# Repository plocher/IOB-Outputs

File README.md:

# IOB-Outputs
## License: CERN Open Hardware Licence v1.2

Output only - non-inverting Open Drain current sink
New IOB design

PNP Ready: Panelized IOB quad "output board", used for driving LEDS and other devices from the [I2C-7311](/pages/I2C-7311) IO expansion board

Features:

* 5v or 9-12v supply,
* Open Drain outputs
* pins are active low

IO4:

* pin 1: 5vDC
* pin 2: !OUT1
* pin 3: !OUT2
* pin 4: !OUT3
* pin 5: !OUT4
* pin 6: GND

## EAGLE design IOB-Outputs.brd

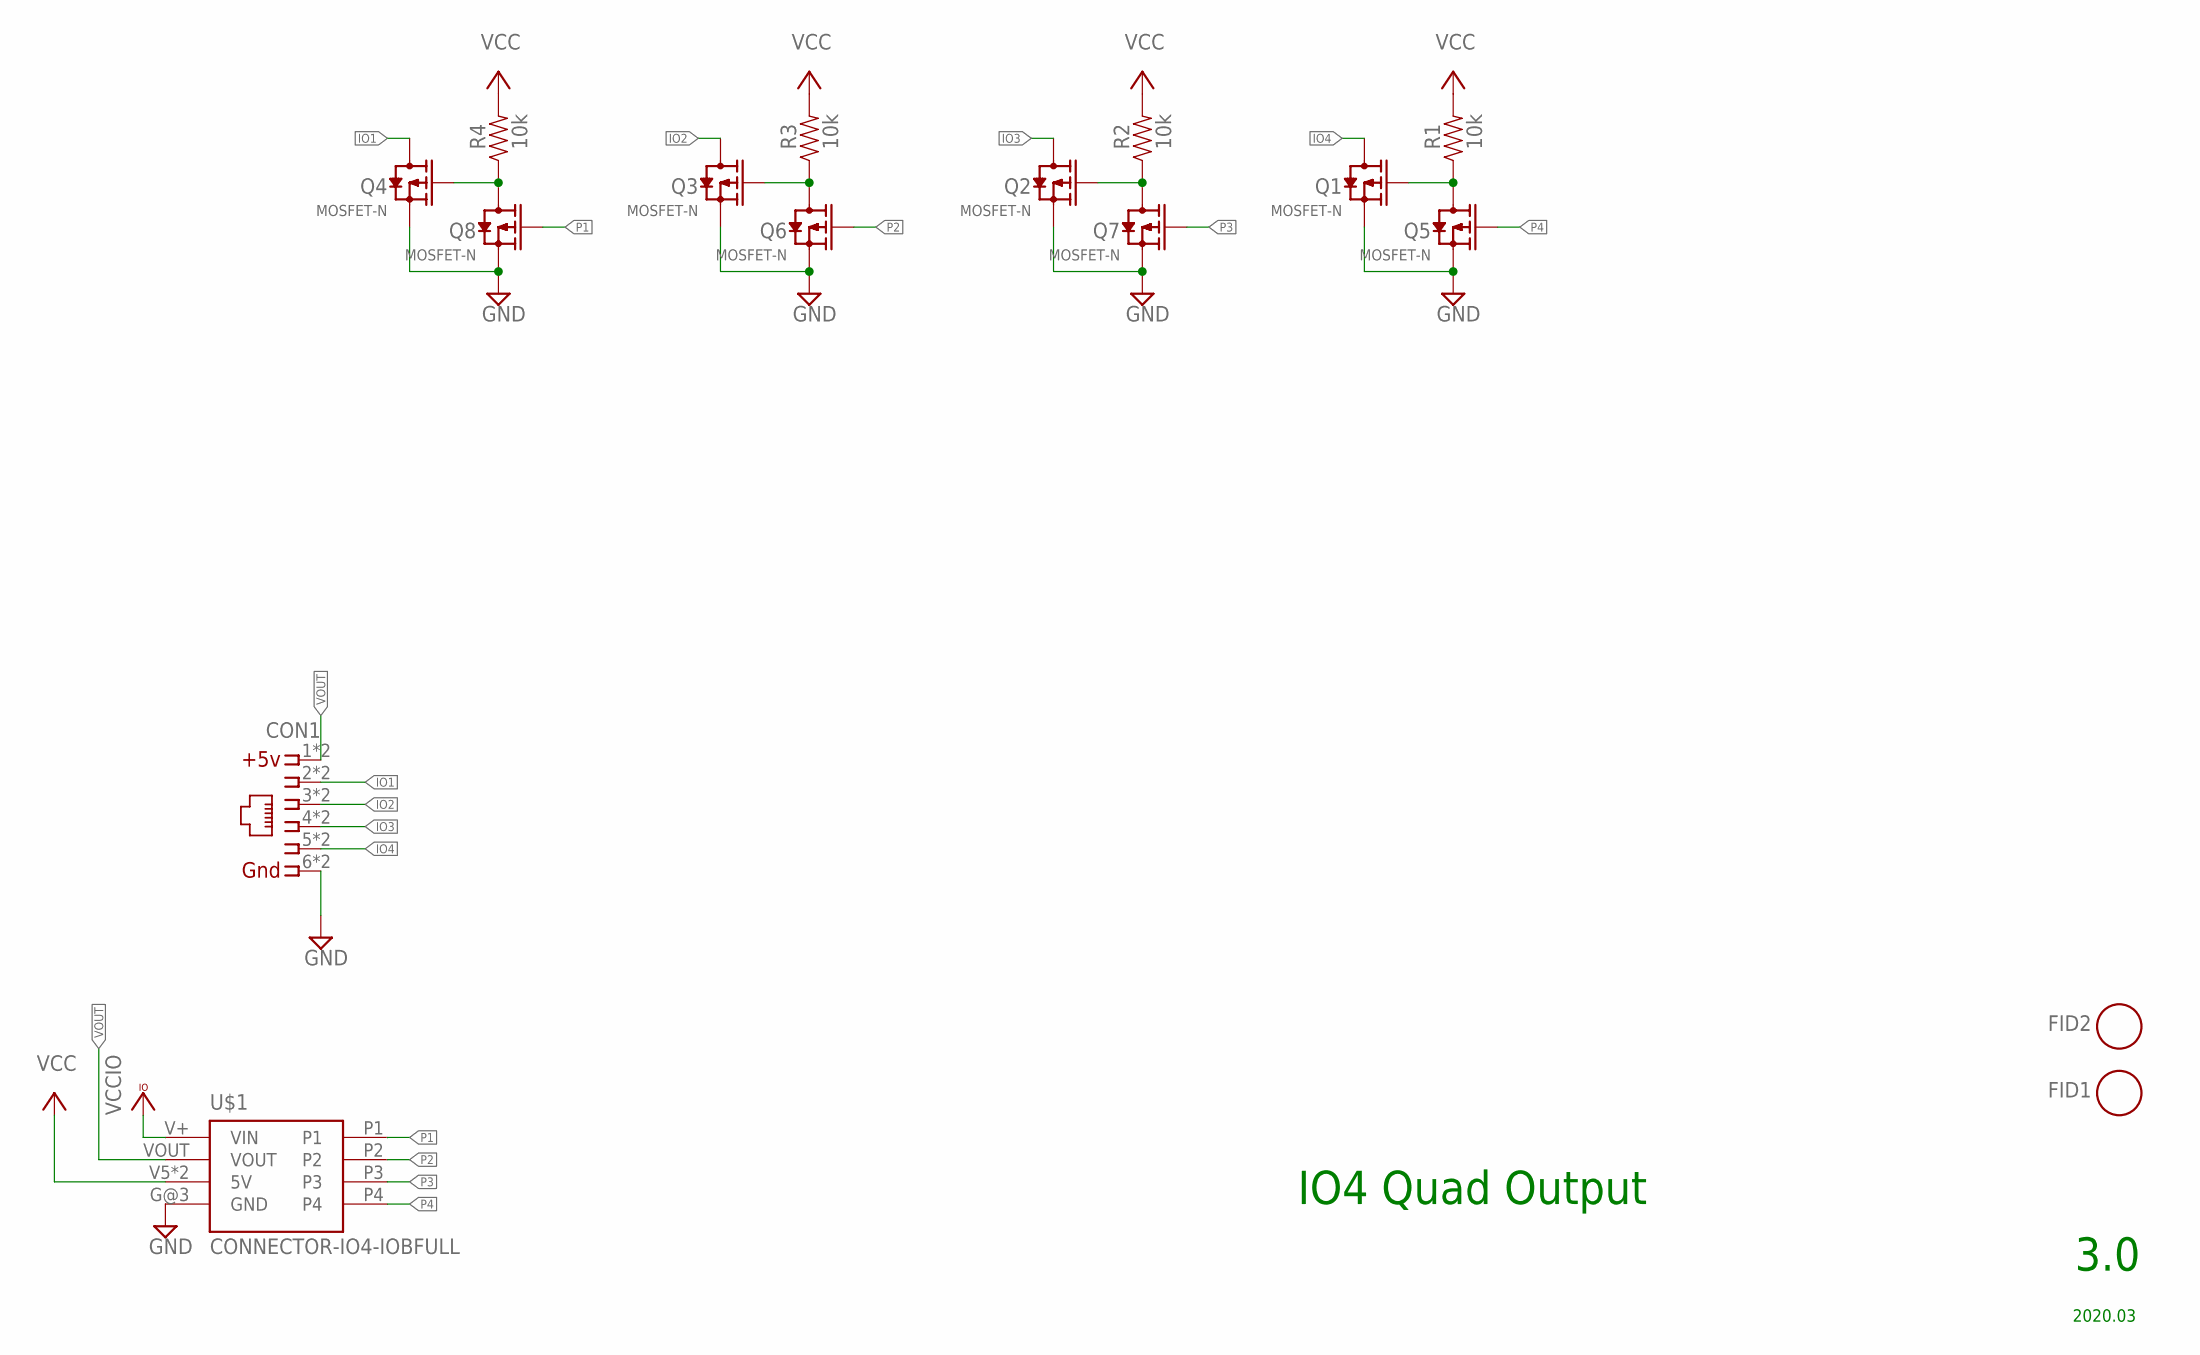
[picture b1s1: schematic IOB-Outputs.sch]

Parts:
CON1: CONNECTOR-IO4IPINS; RJ24-INVERTED-PINS
FID1, FID2: FIDUCIAL; FIDUCIAL_1MM
Q1, Q2, Q3, Q4, Q5, Q6, Q7, Q8: MOSFET-N; SOT23-3
R1, R2, R3, R4: 10k; 0805-RES
U$1: CONNECTOR-IO4-IOBFULL; IO4-IOB

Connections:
GND: CON1.6, CON1.6@1 (6), Q1.2 (S), Q2.2 (S), Q3.2 (S), Q4.2 (S), Q5.2 (S), Q6.2 (S), Q7.2 (S), Q8.2 (S), U$1.G@3 (GND)
IO1: CON1.2, CON1.2@1 (2), Q4.3 (D)
IO2: CON1.3, CON1.3@1 (3), Q3.3 (D)
IO3: CON1.4, CON1.4@1 (4), Q2.3 (D)
IO4: CON1.5, CON1.5@1 (5), Q1.3 (D)
unnamed: Q4.1 (G), Q8.3 (D), R4.1
unnamed: Q3.1 (G), Q6.3 (D), R3.1
unnamed: Q2.1 (G), Q7.3 (D), R2.1
unnamed: Q1.1 (G), Q5.3 (D), R1.1
P1: Q8.1 (G), U$1.P1
P2: Q6.1 (G), U$1.P2
P3: Q7.1 (G), U$1.P3
P4: Q5.1 (G), U$1.P4
VCC: R1.2, R2.2, R3.2, R4.2, U$1.V5 (5V), U$1.V5@1 (5V)
VIN: U$1.V+ (VIN)
VOUT: CON1.1, CON1.1@1 (1), U$1.VOUT

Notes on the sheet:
IO4 Quad Output
3.0
2020.03

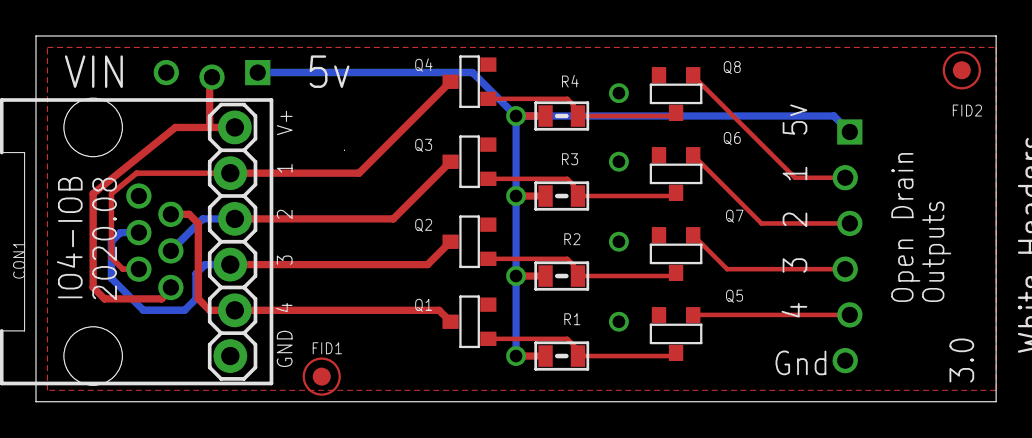
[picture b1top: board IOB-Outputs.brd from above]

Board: 2 copper layers, 53.3 x 20.3 mm, 16 parts (0 on the bottom side), 15 nets.

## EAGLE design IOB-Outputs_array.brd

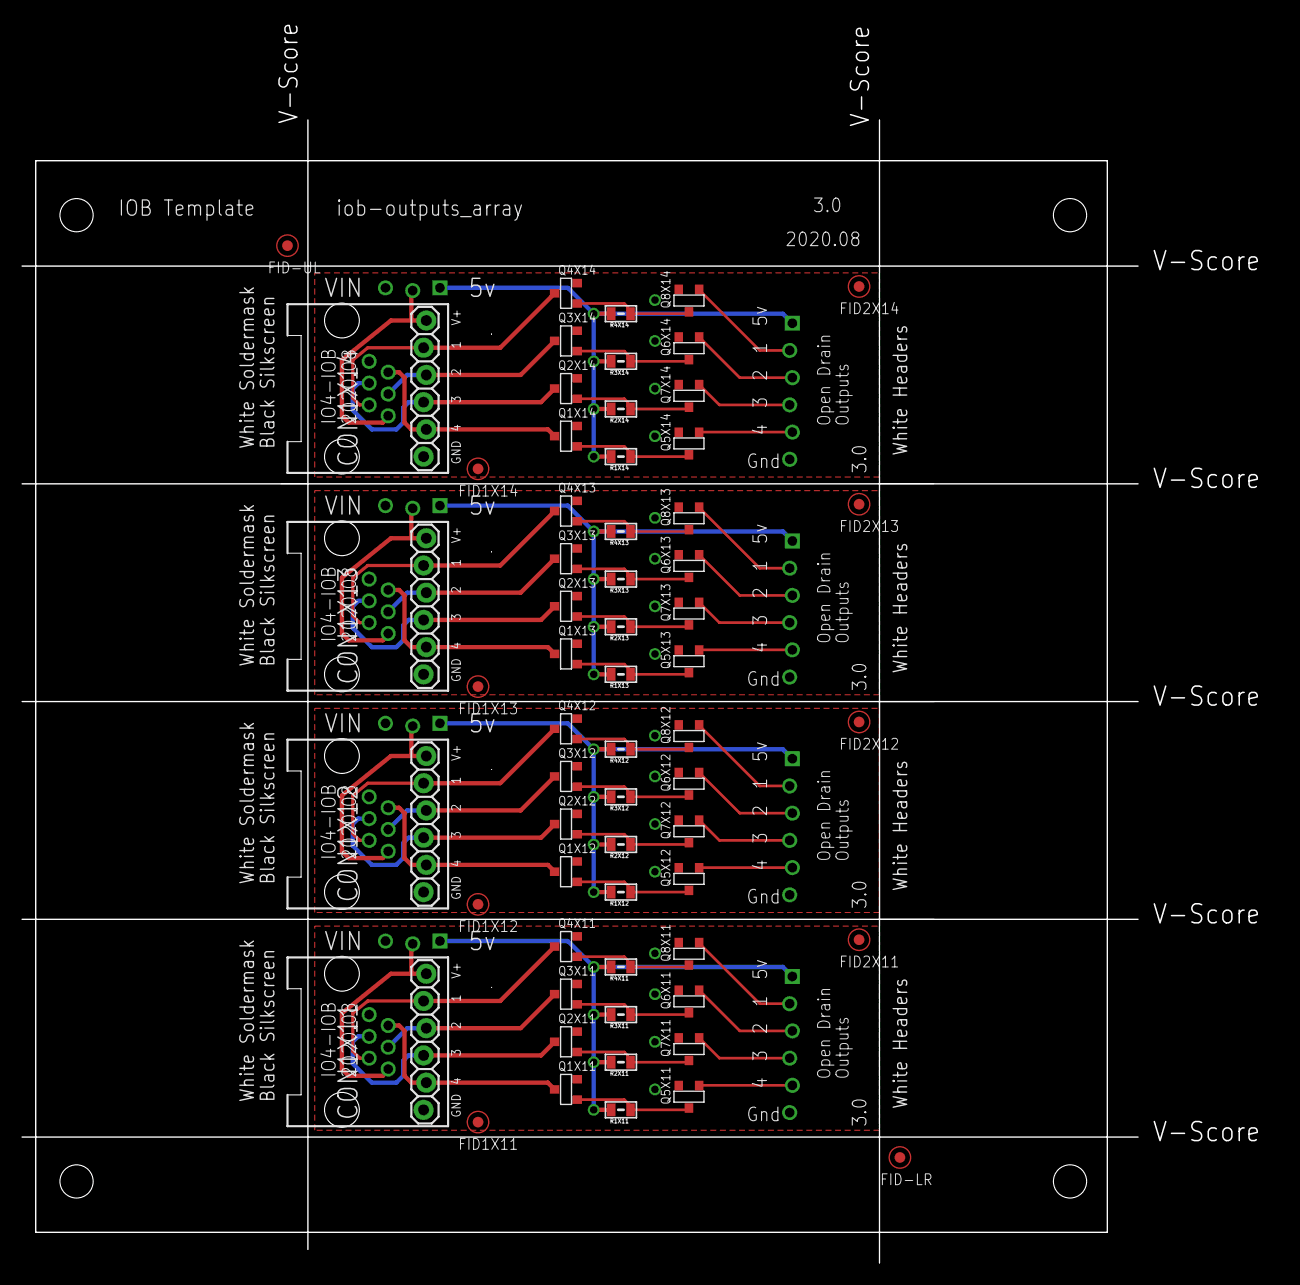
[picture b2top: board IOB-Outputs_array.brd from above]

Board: 2 copper layers, 117.2 x 115.8 mm, 67 parts (0 on the bottom side), 60 nets.

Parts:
CON1X11, CON1X12, CON1X13, CON1X14: RJ24-INVERTED-PINS
FID1X11, FID1X12, FID1X13, FID1X14, FID2X11, FID2X12, FID2X13, FID2X14: FIDUCIAL; FIDUCIAL_1MM
FID-LR: FIDUCIAL; FIDUCIAL_1MM
FID-UL: FIDUCIAL; FIDUCIAL_1MM
Q1X11, Q1X12, Q1X13, Q1X14, Q2X11, Q2X12, Q2X13, Q2X14, Q3X11, Q3X12, Q3X13, Q3X14, Q4X11, Q4X12, Q4X13, Q4X14, Q5X11, Q5X12, Q5X13, Q5X14, Q6X11, Q6X12, Q6X13, Q6X14, Q7X11, Q7X12, Q7X13, Q7X14, Q8X11, Q8X12, Q8X13, Q8X14: MOSFET-N; SOT23-3
R1X11, R1X12, R1X13, R1X14, R2X11, R2X12, R2X13, R2X14, R3X11, R3X12, R3X13, R3X14, R4X11, R4X12, R4X13, R4X14: 10k; 0805-RES
R8X1: BOARD-DINRAIL-3.17IN-H4X-IOB
U$1X11, U$1X12, U$1X13, U$1X14: CONNECTOR-IO4-IOBFULL; IO4-IOB

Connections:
GNDX11: CON1X11.6, CON1X11.6@1, Q1X11.2, Q2X11.2, Q3X11.2, Q4X11.2, Q5X11.2, Q6X11.2, Q7X11.2, Q8X11.2, U$1X11.G@3
GNDX12: CON1X12.6, CON1X12.6@1, Q1X12.2, Q2X12.2, Q3X12.2, Q4X12.2, Q5X12.2, Q6X12.2, Q7X12.2, Q8X12.2, U$1X12.G@3
GNDX13: CON1X13.6, CON1X13.6@1, Q1X13.2, Q2X13.2, Q3X13.2, Q4X13.2, Q5X13.2, Q6X13.2, Q7X13.2, Q8X13.2, U$1X13.G@3
GNDX14: CON1X14.6, CON1X14.6@1, Q1X14.2, Q2X14.2, Q3X14.2, Q4X14.2, Q5X14.2, Q6X14.2, Q7X14.2, Q8X14.2, U$1X14.G@3
IO1X11: CON1X11.2, CON1X11.2@1, Q4X11.3
IO1X12: CON1X12.2, CON1X12.2@1, Q4X12.3
IO1X13: CON1X13.2, CON1X13.2@1, Q4X13.3
IO1X14: CON1X14.2, CON1X14.2@1, Q4X14.3
IO2X11: CON1X11.3, CON1X11.3@1, Q3X11.3
IO2X12: CON1X12.3, CON1X12.3@1, Q3X12.3
IO2X13: CON1X13.3, CON1X13.3@1, Q3X13.3
IO2X14: CON1X14.3, CON1X14.3@1, Q3X14.3
IO3X11: CON1X11.4, CON1X11.4@1, Q2X11.3
IO3X12: CON1X12.4, CON1X12.4@1, Q2X12.3
IO3X13: CON1X13.4, CON1X13.4@1, Q2X13.3
IO3X14: CON1X14.4, CON1X14.4@1, Q2X14.3
IO4X11: CON1X11.5, CON1X11.5@1, Q1X11.3
IO4X12: CON1X12.5, CON1X12.5@1, Q1X12.3
IO4X13: CON1X13.5, CON1X13.5@1, Q1X13.3
IO4X14: CON1X14.5, CON1X14.5@1, Q1X14.3
unnamed: Q4X11.1, Q8X11.3, R4X11.1
unnamed: Q4X12.1, Q8X12.3, R4X12.1
unnamed: Q4X13.1, Q8X13.3, R4X13.1
unnamed: Q4X14.1, Q8X14.3, R4X14.1
unnamed: Q3X11.1, Q6X11.3, R3X11.1
unnamed: Q3X12.1, Q6X12.3, R3X12.1
unnamed: Q3X13.1, Q6X13.3, R3X13.1
unnamed: Q3X14.1, Q6X14.3, R3X14.1
unnamed: Q2X11.1, Q7X11.3, R2X11.1
unnamed: Q2X12.1, Q7X12.3, R2X12.1
unnamed: Q2X13.1, Q7X13.3, R2X13.1
unnamed: Q2X14.1, Q7X14.3, R2X14.1
unnamed: Q1X11.1, Q5X11.3, R1X11.1
unnamed: Q1X12.1, Q5X12.3, R1X12.1
unnamed: Q1X13.1, Q5X13.3, R1X13.1
unnamed: Q1X14.1, Q5X14.3, R1X14.1
P1X11: Q8X11.1, U$1X11.P1
P1X12: Q8X12.1, U$1X12.P1
P1X13: Q8X13.1, U$1X13.P1
P1X14: Q8X14.1, U$1X14.P1
P2X11: Q6X11.1, U$1X11.P2
P2X12: Q6X12.1, U$1X12.P2
P2X13: Q6X13.1, U$1X13.P2
P2X14: Q6X14.1, U$1X14.P2
P3X11: Q7X11.1, U$1X11.P3
P3X12: Q7X12.1, U$1X12.P3
P3X13: Q7X13.1, U$1X13.P3
P3X14: Q7X14.1, U$1X14.P3
P4X11: Q5X11.1, U$1X11.P4
P4X12: Q5X12.1, U$1X12.P4
P4X13: Q5X13.1, U$1X13.P4
P4X14: Q5X14.1, U$1X14.P4
VCCX11: R1X11.2, R2X11.2, R3X11.2, R4X11.2, U$1X11.V5, U$1X11.V5@1
VCCX12: R1X12.2, R2X12.2, R3X12.2, R4X12.2, U$1X12.V5, U$1X12.V5@1
VCCX13: R1X13.2, R2X13.2, R3X13.2, R4X13.2, U$1X13.V5, U$1X13.V5@1
VCCX14: R1X14.2, R2X14.2, R3X14.2, R4X14.2, U$1X14.V5, U$1X14.V5@1
VOUTX11: CON1X11.1, CON1X11.1@1, U$1X11.VOUT
VOUTX12: CON1X12.1, CON1X12.1@1, U$1X12.VOUT
VOUTX13: CON1X13.1, CON1X13.1@1, U$1X13.VOUT
VOUTX14: CON1X14.1, CON1X14.1@1, U$1X14.VOUT

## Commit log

2019-12-07 un-spin text
2019-12-09 added graphic
2020-03-06 updated to new IOB design
2020-03-06 bump version
2020-03-06 new IOB design
2020-03-07 updated changelog
2020-05-04 updated tags
2020-05-04 panelized
2020-08-09 fixed SPCoast.lbr diode orientation
2020-08-09 Added missing values
2020-08-11 normalized silkscreen layout across IOBs
2020-08-11 move text from DOCU to TPLACE
2020-08-11 SPCoast Color Pallette
2020-08-12 added board template
